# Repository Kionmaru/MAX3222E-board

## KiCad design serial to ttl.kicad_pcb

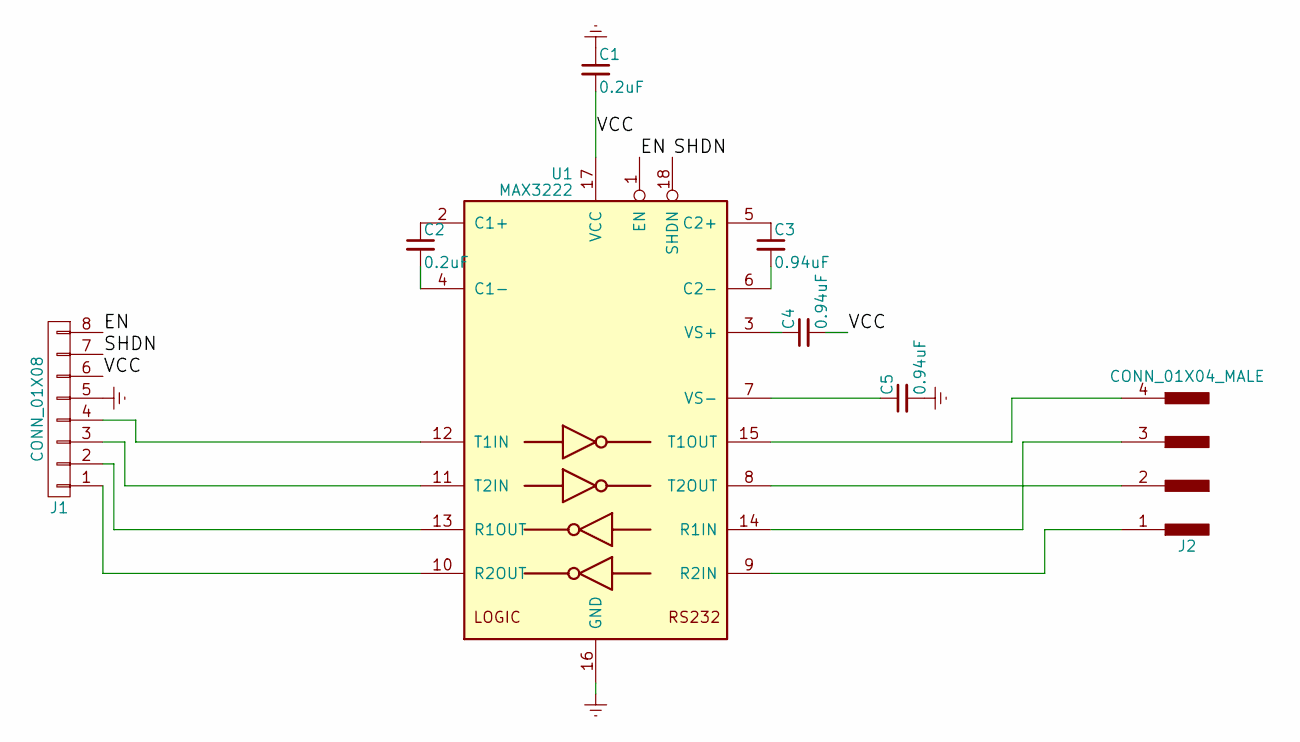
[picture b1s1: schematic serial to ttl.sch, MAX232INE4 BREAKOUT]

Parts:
C1, C2: 0.2uF; R_0805_HandSoldering
C3, C4, C5: 0.94uF; R_0805_HandSoldering
J1: CONN_01X08; Socket_Strip_Straight_1x08_Pitch2.54mm
J2: CONN_01X04_MALE; Socket_Strip_Straight_1x04_Pitch2.54mm
U1: MAX3222; DIP-18_W7.62mm

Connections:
/EN: J1.8, U1.1 (EN)
/SHDN: J1.7, U1.18 (SHDN)
/VCC: C1.2, C4.2, J1.6, U1.17 (VCC)
Earth: C1.1, C5.2, J1.5, U1.16 (GND)
unnamed: C2.1, U1.2 (C1+)
unnamed: C2.2, U1.4 (C1-)
unnamed: C3.1, U1.5 (C2+)
unnamed: C3.2, U1.6 (C2-)
unnamed: C4.1, U1.3 (VS+)
unnamed: C5.1, U1.7 (VS-)
unnamed: J1.1, U1.10 (R2OUT)
unnamed: J1.2, U1.13 (R1OUT)
unnamed: J1.3, U1.11 (T2IN)
unnamed: J1.4, U1.12 (T1IN)
unnamed: J2.1, U1.9 (R2IN)
unnamed: J2.2, U1.8 (T2OUT)
unnamed: J2.3, U1.14 (R1IN)
unnamed: J2.4, U1.15 (T1OUT)

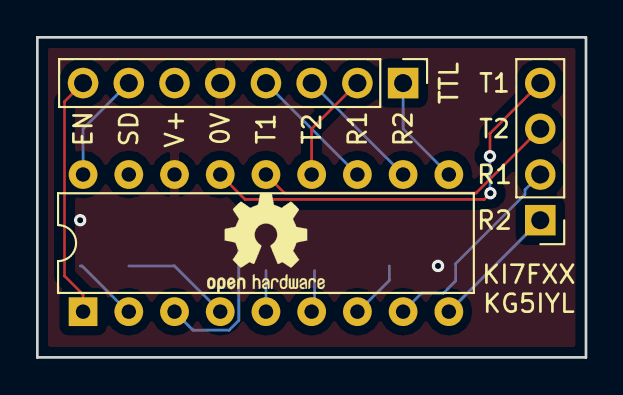
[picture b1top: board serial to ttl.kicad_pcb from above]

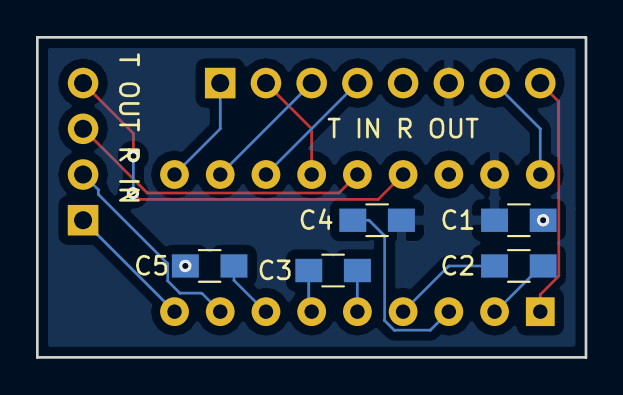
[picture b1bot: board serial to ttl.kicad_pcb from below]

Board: 2 copper layers, 30.5 x 17.8 mm, 8 parts (5 on the bottom side), 18 nets.

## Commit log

2017-05-25 OSHW Serial to TTL converter board
    Initial commit
